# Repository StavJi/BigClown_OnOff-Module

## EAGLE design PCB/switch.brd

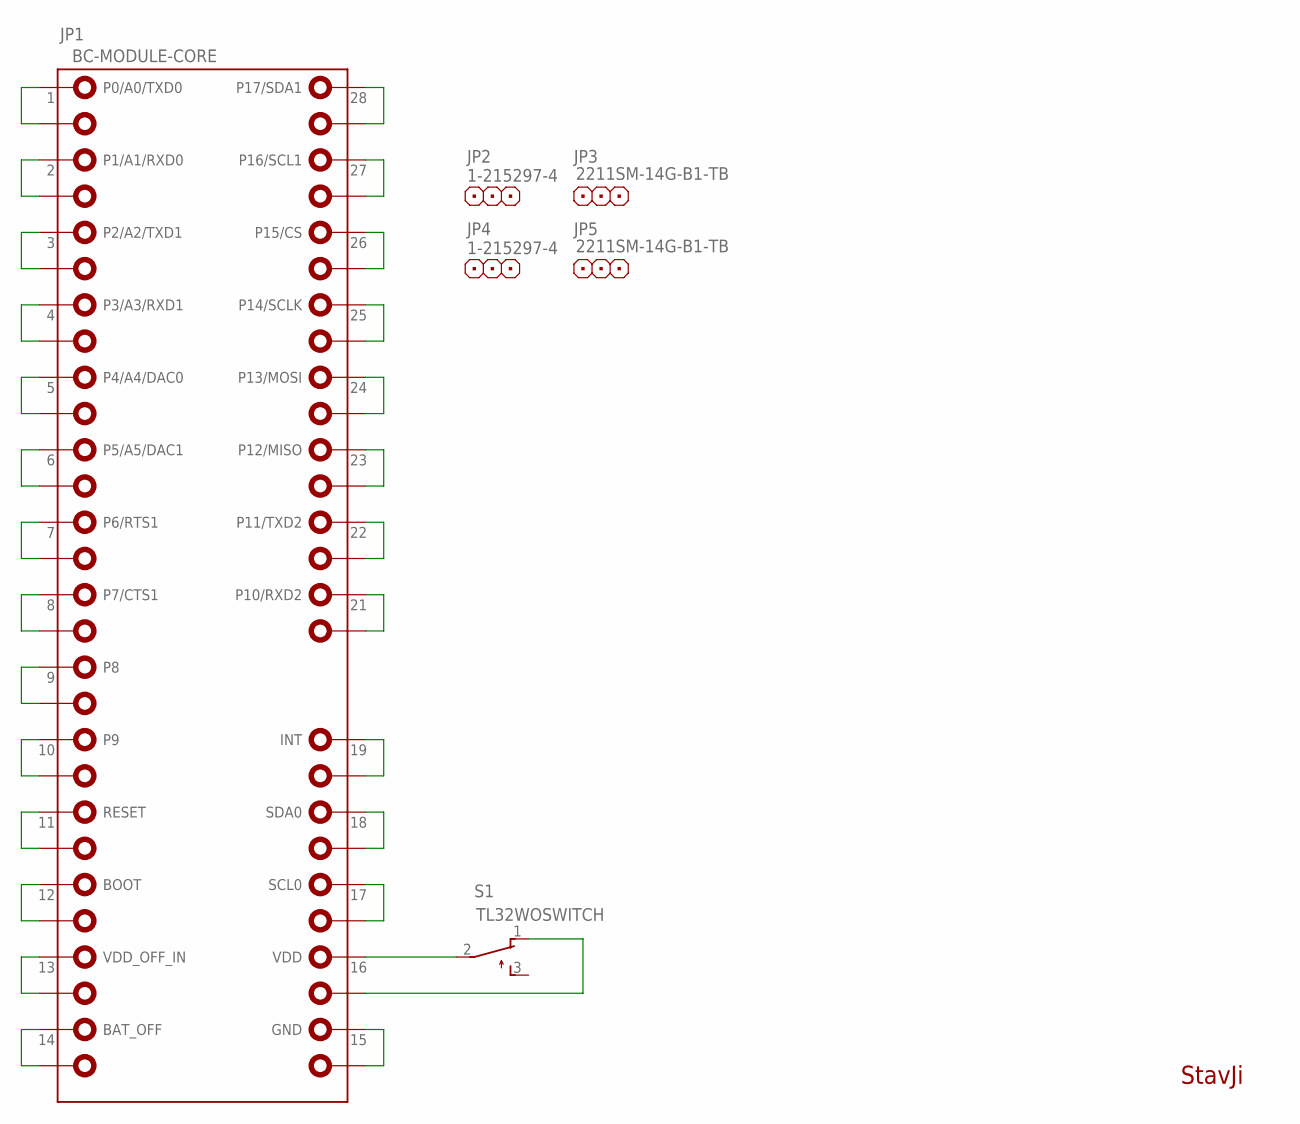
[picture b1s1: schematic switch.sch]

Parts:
JP1: BC-MODULE-CORE; BC-MODULE-CORE-SMD-TOP-BOT
JP2, JP4: 1-215297-4; 1X14_WITHOUT_PAD
JP3, JP5: 2211SM-14G-B1-TB; 1X14_WITHOUT_PAD
S1: TL32WOSWITCH; SWITCH

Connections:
unnamed: JP1.1 (P0/A0/TXD0), JP1.1B (P0/A0/TXD0_B)
unnamed: JP1.2 (P1/A1/RXD0), JP1.2B (P1/A1/RXD0_B)
unnamed: JP1.3 (P2/A2/TXD1), JP1.3B (P2/A2/TXD1_B)
unnamed: JP1.4 (P3/A3/RXD1), JP1.4B (P3/A3/RXD1_B)
unnamed: JP1.5 (P4/A4/DAC0), JP1.5B (P4/A4/DAC0_B)
unnamed: JP1.6 (P5/A5/DAC1), JP1.6B (P5/A5/DAC1_B)
unnamed: JP1.7 (P6/RTS1), JP1.7B (P6/RTS1_B)
unnamed: JP1.8 (P7/CTS1), JP1.8B (P7/CTS1_B)
unnamed: JP1.9 (P8), JP1.9B (P8_B)
unnamed: JP1.10 (P9), JP1.10B (P9_B)
unnamed: JP1.11 (RESET), JP1.11B (RESET_B)
unnamed: JP1.12 (BOOT), JP1.12B (BOOT_B)
unnamed: JP1.13 (VDD_OFF_IN), JP1.13B (VDD_OFF_IN_B)
unnamed: JP1.14 (BAT_OFF), JP1.14B (BAT_OFF_B)
unnamed: JP1.28 (P17/SDA1), JP1.28B (P17/SDA1_B)
unnamed: JP1.27 (P16/SCL1), JP1.27B (P16/SCL1_B)
unnamed: JP1.26 (P15/CS), JP1.26B (P15/CS_B)
unnamed: JP1.25 (P14/SCLK), JP1.25B (P14/SCLK_B)
unnamed: JP1.24 (P13/MOSI), JP1.24B (P13/MOSI_B)
unnamed: JP1.23 (P12/MISO), JP1.23B (P12/MISO_B)
unnamed: JP1.22 (P11/TXD2), JP1.22B (P11/TXD2_B)
unnamed: JP1.21 (P10/RXD2), JP1.21B (P10/RXD2_B)
unnamed: JP1.19 (INT), JP1.19B (INT_B)
unnamed: JP1.18 (SDA0), JP1.18B (SDA0_B)
unnamed: JP1.17 (SCL0), JP1.17B (SCL0_B)
unnamed: JP1.15 (GND), JP1.15B (GND_B)
unnamed: JP1.16B (VDD_B), S1.1 (O)
unnamed: JP1.16 (VDD), S1.2

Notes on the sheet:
StavJi

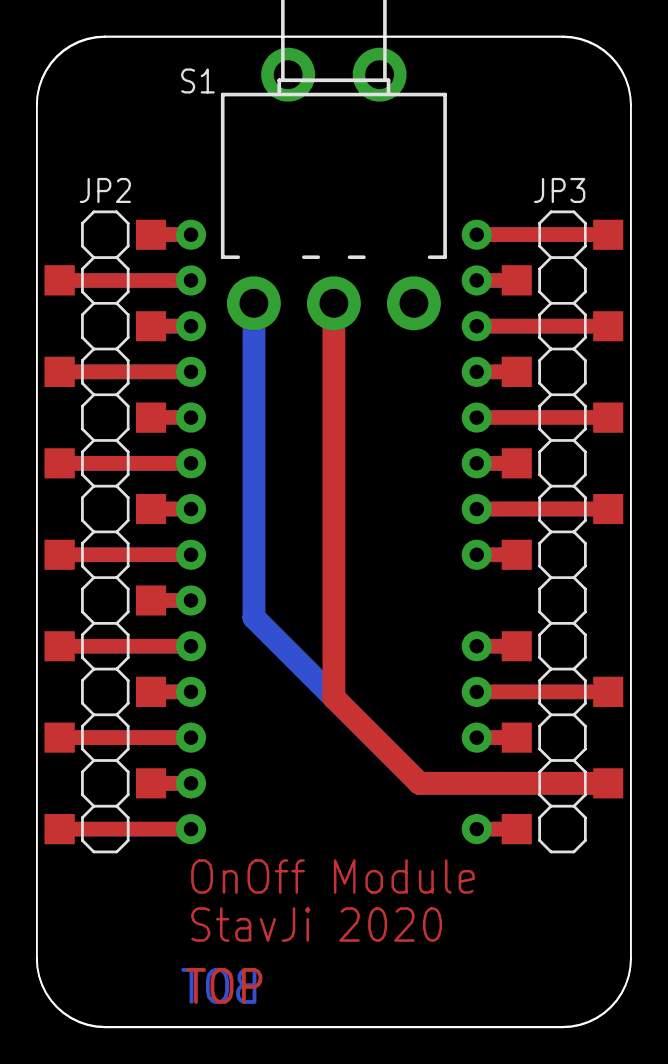
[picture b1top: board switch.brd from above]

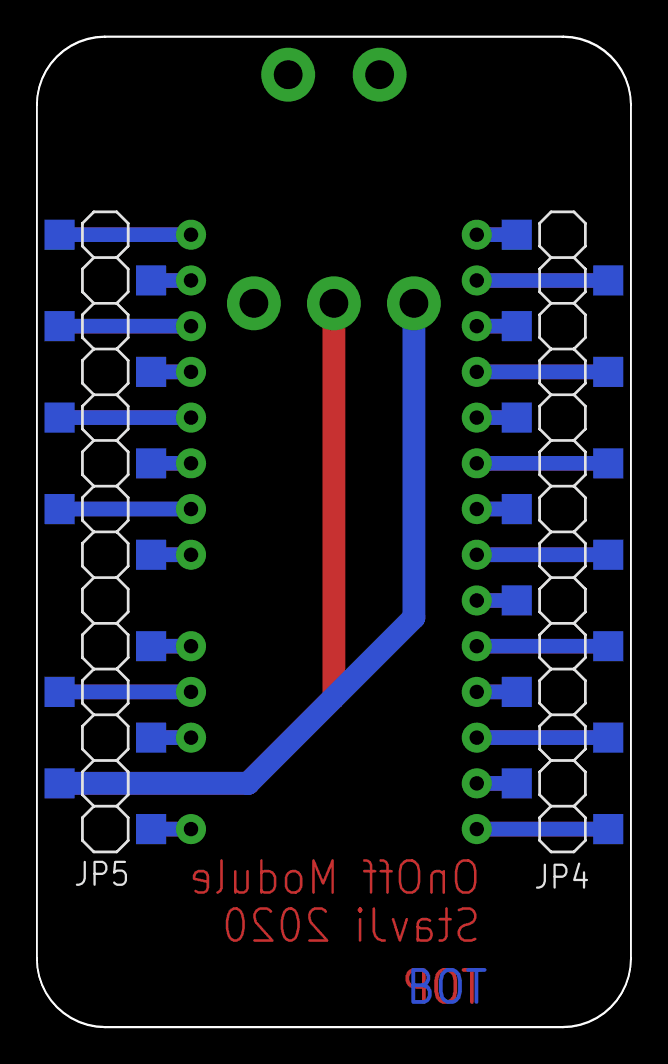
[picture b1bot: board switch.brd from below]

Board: 2 copper layers, 33.0 x 55.0 mm, 6 parts (2 on the bottom side), 28 nets.

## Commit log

2020-12-09 add draft of OnOff module PCB for BigClown Core module
2020-12-09 feat: add header package ontline
2020-12-10 feat: add case and fotos
2020-12-10 add picture to readme
2020-12-10 fix: switch package ontline
2021-03-16 fix: typo
